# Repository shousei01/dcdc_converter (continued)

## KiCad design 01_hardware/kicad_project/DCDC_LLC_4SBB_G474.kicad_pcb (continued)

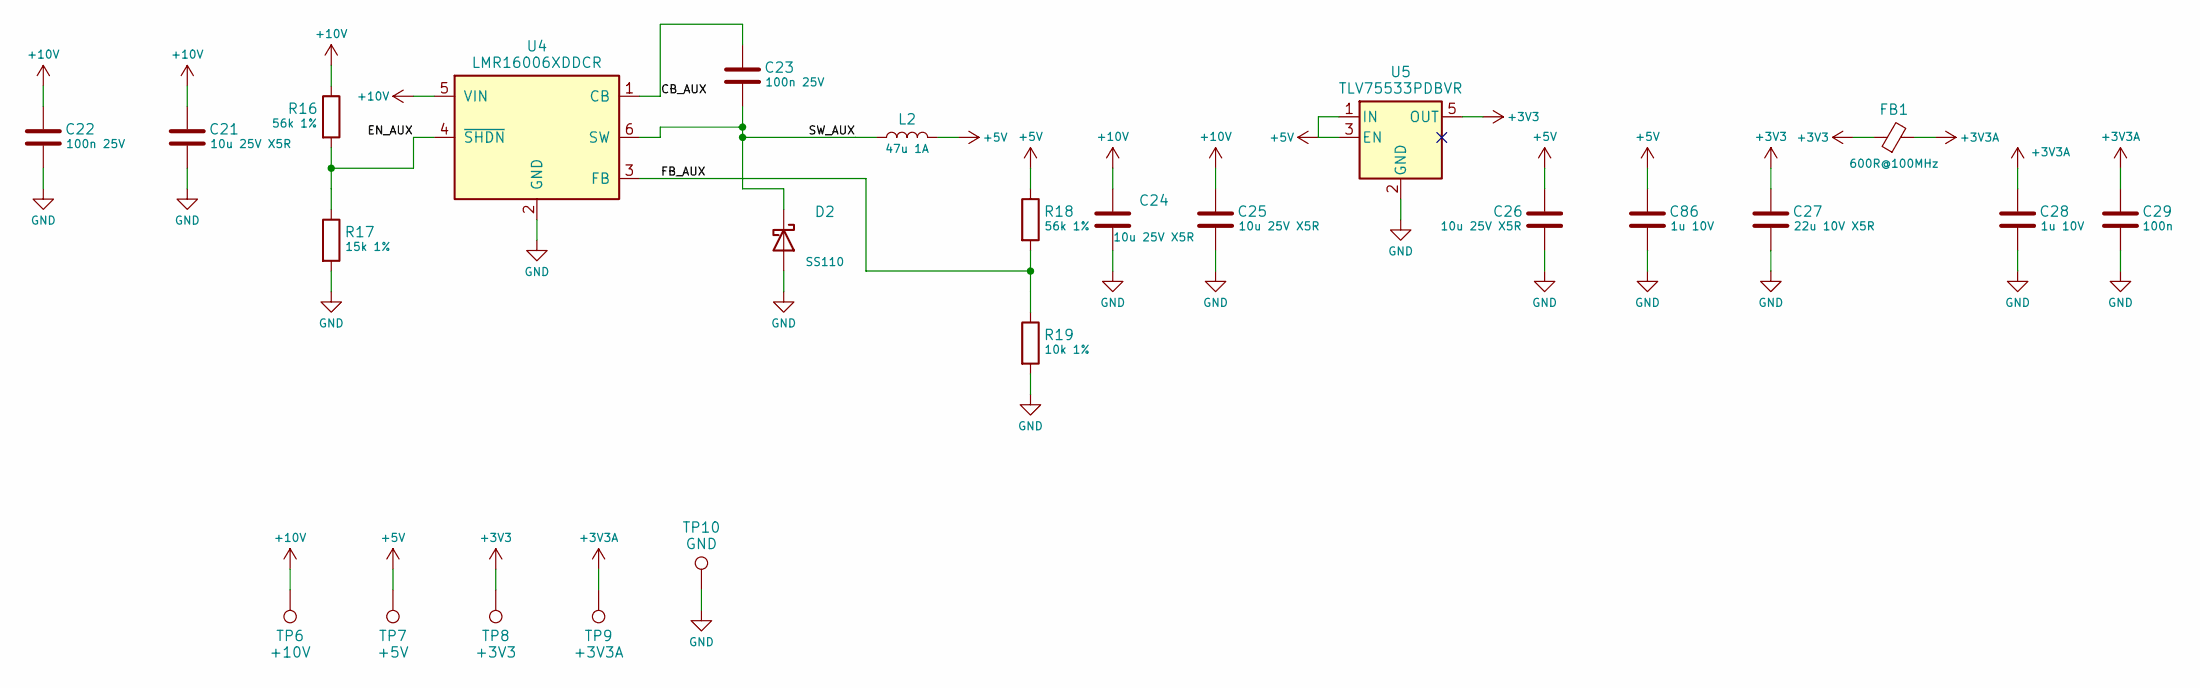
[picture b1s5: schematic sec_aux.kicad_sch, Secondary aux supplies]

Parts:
C21, C24, C25, C26: 10u 25V X5R; C_0805_2012Metric; MPN 10u 25V X5R; LCSC C15850
C22, C23: 100n 25V; C_0402_1005Metric; MPN 100n 25V; LCSC C307331
C27: 22u 10V X5R; C_0805_2012Metric; MPN 22u 10V X5R; LCSC C45783
C28, C86: 1u 10V; C_0402_1005Metric; MPN 1u 10V; LCSC C20539426
C29: 100n; C_0402_1005Metric; MPN 100n; LCSC C307331
D2: SS110; D_SMA; MPN SS110; LCSC C2482
FB1: 600R@100MHz; L_0603_1608Metric; MPN BLM18KG601SN1D; LCSC C85833
L2: 47u 1A; L_Sunlord_SWPA5040S; MPN FNR5040S470MT; LCSC C167974
R16, R18: 56k 1%; R_0402_1005Metric; MPN 56k 1%; LCSC C25796
R17: 15k 1%; R_0402_1005Metric; MPN 15k 1%; LCSC C25756
R19: 10k 1%; R_0402_1005Metric; MPN 10k 1%; LCSC C2906861
TP6: +10V; TestPoint_Pad_D1.5mm; MPN PCB pad, no part
TP7: +5V; TestPoint_Pad_D1.5mm; MPN PCB pad, no part
TP8: +3V3; TestPoint_Pad_D1.5mm; MPN PCB pad, no part
TP9: +3V3A; TestPoint_Pad_D1.5mm; MPN PCB pad, no part
TP10: GND; TestPoint_Pad_D1.5mm; MPN PCB pad, no part
U4: LMR16006XDDCR; SOT-23-6; MPN LMR16006XDDCR; LCSC C87080
U5: TLV75533PDBVR; SOT-23-5; MPN TLV75533PDBVR; LCSC C404027

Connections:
+3V3: C27.1, FB1.1, TP8.1, U5.5 (OUT); also elsewhere on the board
+3V3A: C28.1, C29.1, FB1.2, TP9.1; also elsewhere on the board
+5V: C26.1, C86.1, L2.2, R18.1, TP7.1, U5.1 (IN), U5.3 (EN); also elsewhere on the board
+10V: C21.1, C22.1, C24.1, C25.1, R16.1, TP6.1, U4.5 (VIN); also elsewhere on the board
CB_AUX: C23.1, U4.1 (CB)
EN_AUX: R16.2, R17.1, U4.4 (~SHDN)
FB_AUX: R18.2, R19.1, U4.3 (FB)
GND: C21.2, C22.2, C24.2, C25.2, C26.2, C27.2, C28.2, C29.2, C86.2, D2.2 (A), R17.2, R19.2, TP10.1, U4.2 (GND), U5.2 (GND); also elsewhere on the board
SW_AUX: C23.2, D2.1 (K), L2.1, U4.6 (SW)

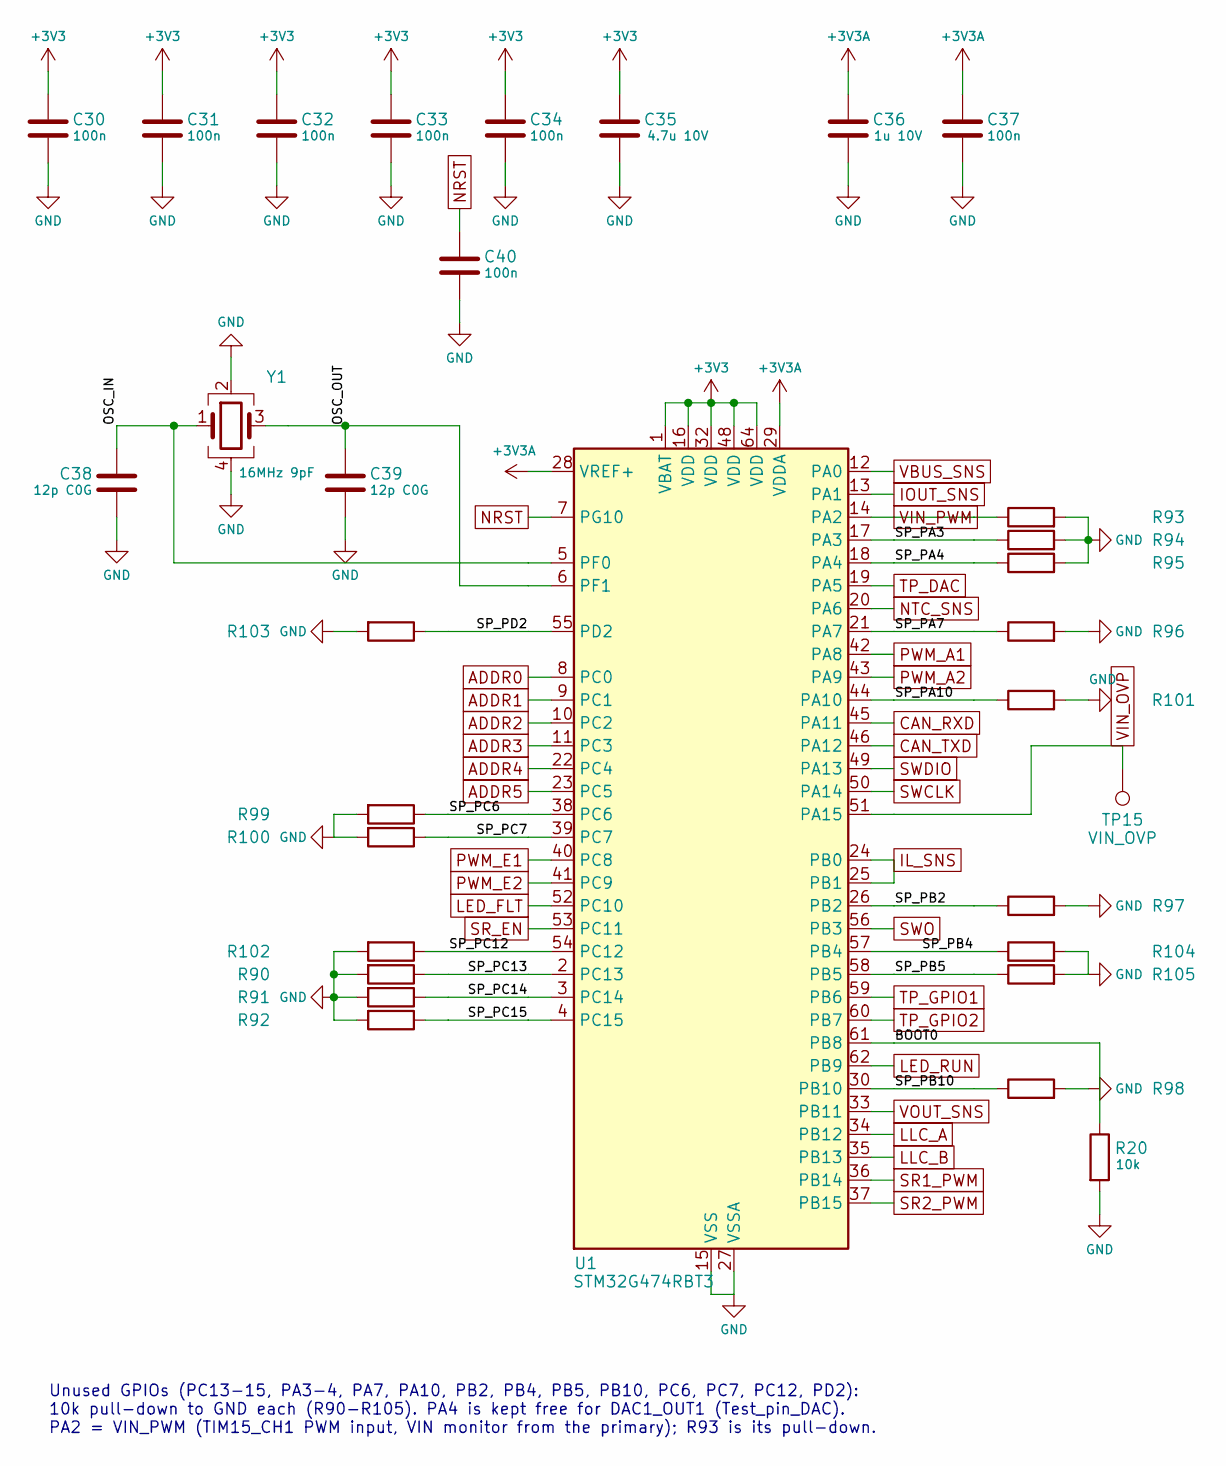
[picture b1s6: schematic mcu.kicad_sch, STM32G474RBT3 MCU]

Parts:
C30, C31, C32, C33, C34, C37, C40: 100n; C_0402_1005Metric; MPN 100n; LCSC C307331
C35: 4.7u 10V; C_0603_1608Metric; MPN 4.7u 10V; LCSC C19666
C36: 1u 10V; C_0402_1005Metric; MPN 1u 10V; LCSC C20539426
C38, C39: 12p C0G; C_0402_1005Metric; MPN 12p C0G; LCSC C1547
R20, R90, R91, R92, R93, R94, R95, R96, R97, R98, R99, R100, R101, R102, R103, R104, R105: 10k; R_0402_1005Metric; MPN 10k; LCSC C2906861
TP15: VIN_OVP; TestPoint_Pad_D1.5mm; MPN PCB pad, no part
U1: STM32G474RBT3; LQFP-64_10x10mm_P0.5mm; MPN STM32G474RBT3; LCSC C1235414
Y1: 16MHz 9pF; Crystal_SMD_3225-4Pin_3.2x2.5mm; MPN X322516MLB4SI; LCSC C13738

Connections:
+3V3: C30.1, C31.1, C32.1, C33.1, C34.1, C35.1, U1.1 (VBAT), U1.16 (VDD), U1.32 (VDD), U1.48 (VDD), U1.64 (VDD); also elsewhere on the board
+3V3A: C36.1, C37.1, U1.28 (VREF+), U1.29 (VDDA); also elsewhere on the board
ADDR0: U1.8 (PC0); also elsewhere on the board
ADDR1: U1.9 (PC1); also elsewhere on the board
ADDR2: U1.10 (PC2); also elsewhere on the board
ADDR3: U1.11 (PC3); also elsewhere on the board
ADDR4: U1.22 (PC4); also elsewhere on the board
ADDR5: U1.23 (PC5); also elsewhere on the board
BOOT0: R20.1, U1.61 (PB8)
CAN_RXD: U1.45 (PA11); also elsewhere on the board
CAN_TXD: U1.46 (PA12); also elsewhere on the board
GND: C30.2, C31.2, C32.2, C33.2, C34.2, C35.2, C36.2, C37.2, C38.2, C39.2, C40.2, R20.2, R90.2, R91.2, R92.2, R93.2, R94.2, R95.2, R96.2, R97.2, R98.2, R99.2, R100.2, R101.2, R102.2, R103.2, R104.2, R105.2, U1.15 (VSS), U1.27 (VSSA), U1.31 (VSS), U1.47 (VSS), U1.63 (VSS), Y1.2, Y1.4; also elsewhere on the board
IL_SNS: U1.24 (PB0), U1.25 (PB1); also elsewhere on the board
IOUT_SNS: U1.13 (PA1); also elsewhere on the board
LED_FLT: U1.52 (PC10); also elsewhere on the board
LED_RUN: U1.62 (PB9); also elsewhere on the board
LLC_A: U1.34 (PB12); also elsewhere on the board
LLC_B: U1.35 (PB13); also elsewhere on the board
NRST: C40.1, U1.7 (PG10); also elsewhere on the board
NTC_SNS: U1.20 (PA6); also elsewhere on the board
OSC_IN: C38.1, U1.5 (PF0), Y1.1
OSC_OUT: C39.1, U1.6 (PF1), Y1.3
PWM_A1: U1.42 (PA8); also elsewhere on the board
PWM_A2: U1.43 (PA9); also elsewhere on the board
PWM_E1: U1.40 (PC8); also elsewhere on the board
PWM_E2: U1.41 (PC9); also elsewhere on the board
SP_PA3: R94.1, U1.17 (PA3)
SP_PA4: R95.1, U1.18 (PA4)
SP_PA7: R96.1, U1.21 (PA7)
SP_PA10: R101.1, U1.44 (PA10)
SP_PB2: R97.1, U1.26 (PB2)
SP_PB4: R104.1, U1.57 (PB4)
SP_PB5: R105.1, U1.58 (PB5)
SP_PB10: R98.1, U1.30 (PB10)
SP_PC6: R99.1, U1.38 (PC6)
SP_PC7: R100.1, U1.39 (PC7)
SP_PC12: R102.1, U1.54 (PC12)
SP_PC13: R90.1, U1.2 (PC13)
SP_PC14: R91.1, U1.3 (PC14)
SP_PC15: R92.1, U1.4 (PC15)
SP_PD2: R103.1, U1.55 (PD2)
SR1_PWM: U1.36 (PB14); also elsewhere on the board
SR2_PWM: U1.37 (PB15); also elsewhere on the board
SR_EN: U1.53 (PC11); also elsewhere on the board
SWCLK: U1.50 (PA14); also elsewhere on the board
SWDIO: U1.49 (PA13); also elsewhere on the board
SWO: U1.56 (PB3); also elsewhere on the board
TP_DAC: U1.19 (PA5); also elsewhere on the board
TP_GPIO1: U1.59 (PB6); also elsewhere on the board
TP_GPIO2: U1.60 (PB7); also elsewhere on the board
VBUS_SNS: U1.12 (PA0); also elsewhere on the board
VIN_OVP: TP15.1, U1.51 (PA15); also elsewhere on the board
VIN_PWM: R93.1, U1.14 (PA2); also elsewhere on the board
VOUT_SNS: U1.33 (PB11); also elsewhere on the board

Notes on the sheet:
Unused GPIOs (PC13-15, PA3-4, PA7, PA10, PB2, PB4, PB5, PB10, PC6, PC7, PC12, PD2): 10k pull-down to GND each (R90-R105). PA4 is kept free for DAC1_OUT1 (Test_pin_DAC). PA2 = VIN_PWM (TIM15_CH1 PWM input, VIN monitor from the primary); R93 is its pull-down.

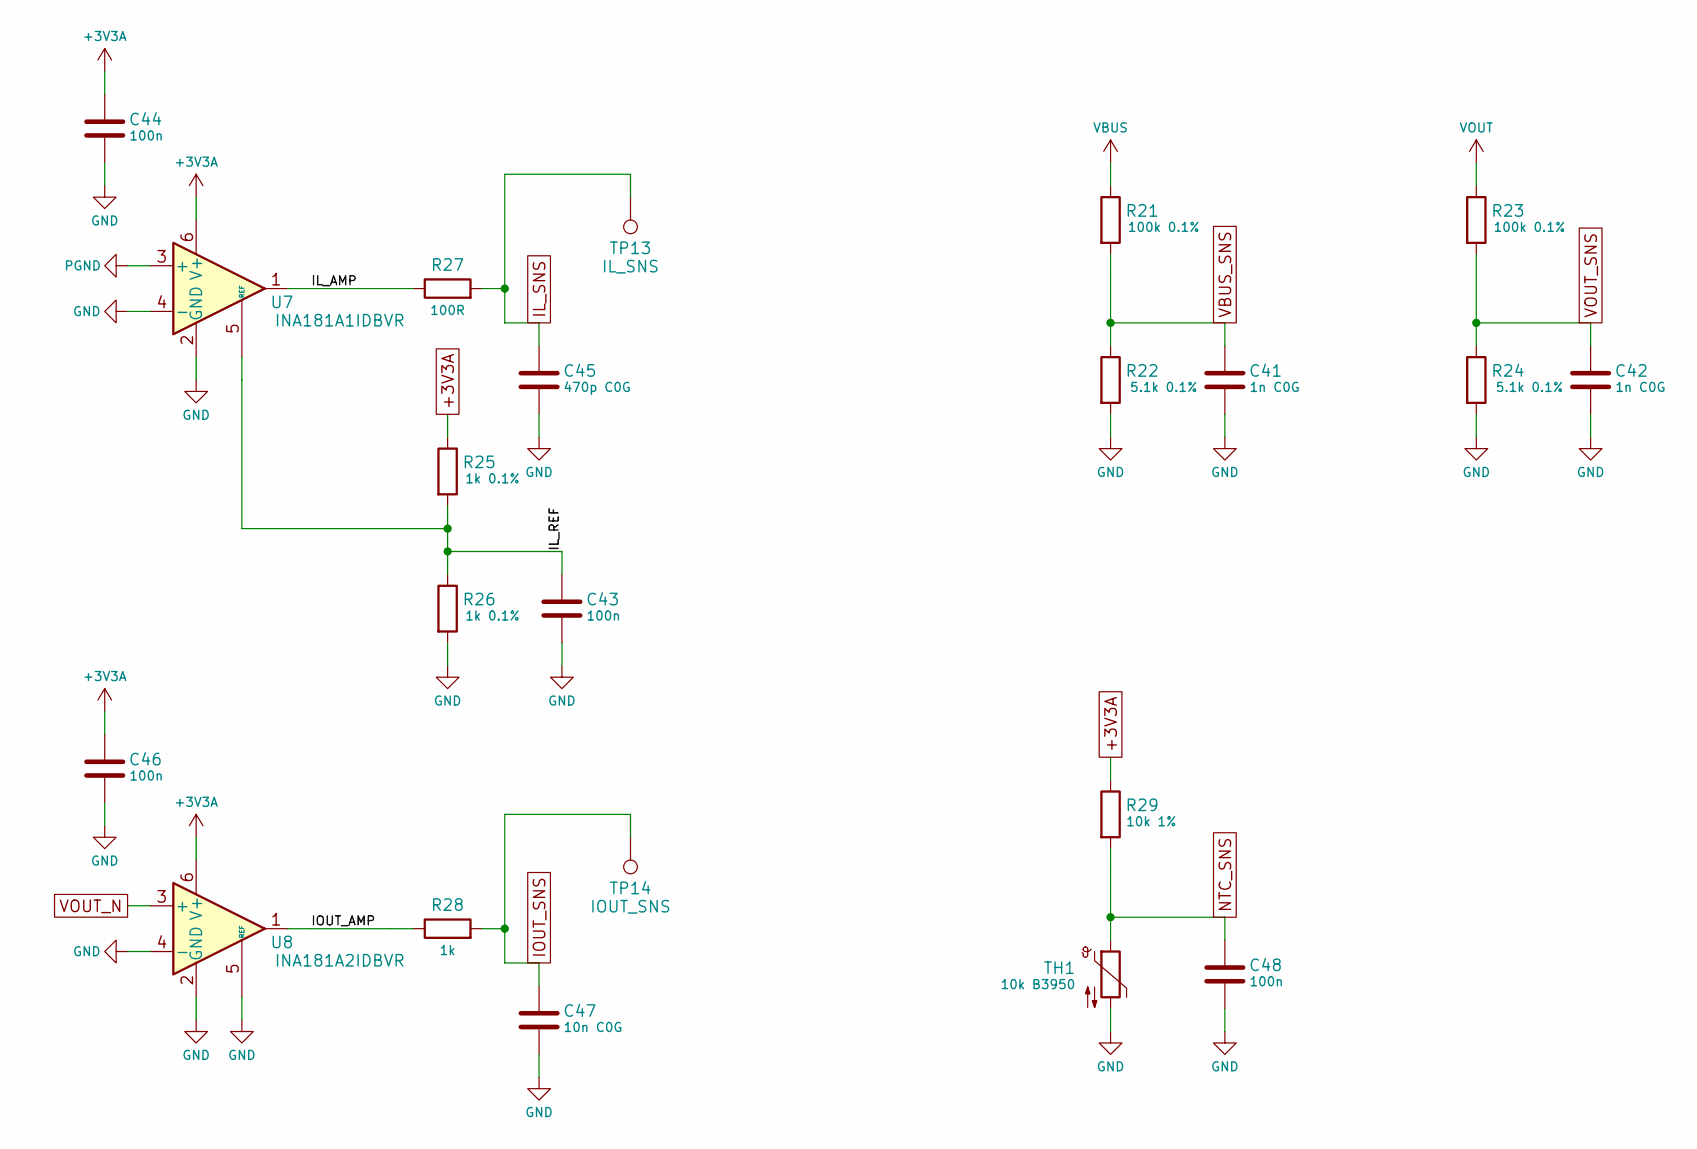
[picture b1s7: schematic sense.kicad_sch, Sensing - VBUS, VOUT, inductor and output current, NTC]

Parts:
C41, C42: 1n C0G; C_0402_1005Metric; MPN 1n C0G; LCSC C113780
C43, C44, C46, C48: 100n; C_0402_1005Metric; MPN 100n; LCSC C307331
C45: 470p C0G; C_0402_1005Metric; MPN 470p C0G; LCSC C106259
C47: 10n C0G; C_0402_1005Metric; MPN 10n C0G; LCSC C22400107
R21, R23: 100k 0.1%; R_0603_1608Metric; MPN 100k 0.1%; LCSC C122538
R22, R24: 5.1k 0.1%; R_0402_1005Metric; MPN 5.1k 0.1%; LCSC C186154
R25, R26: 1k 0.1%; R_0402_1005Metric; MPN 1k 0.1%; LCSC C186137
R27: 100R; R_0402_1005Metric; MPN 100R; LCSC C25076
R28: 1k; R_0402_1005Metric; MPN 1k; LCSC C11702
R29: 10k 1%; R_0402_1005Metric; MPN 10k 1%; LCSC C2906861
TH1: 10k B3950; R_0603_1608Metric; MPN 10k B3950; LCSC C2892547
TP13: IL_SNS; TestPoint_Pad_D1.5mm; MPN PCB pad, no part
TP14: IOUT_SNS; TestPoint_Pad_D1.5mm; MPN PCB pad, no part
U7: INA181A1IDBVR; SOT-23-6; MPN INA181A1IDBVR; LCSC C2058943
U8: INA181A2IDBVR; SOT-23-6; MPN INA181A2IDBVR; LCSC C2058784

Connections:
+3V3A: C44.1, C46.1, R25.1, R29.1, U7.6 (V+), U8.6 (V+); also elsewhere on the board
GND: C41.2, C42.2, C43.2, C44.2, C45.2, C46.2, C47.2, C48.2, R22.2, R24.2, R26.2, TH1.2, U7.2 (GND), U7.4 (-), U8.2 (GND), U8.4 (-), U8.5 (REF); also elsewhere on the board
IL_AMP: R27.1, U7.1
IL_REF: C43.1, R25.2, R26.1, U7.5 (REF)
IL_SNS: C45.1, R27.2, TP13.1; also elsewhere on the board
IOUT_AMP: R28.1, U8.1
IOUT_SNS: C47.1, R28.2, TP14.1; also elsewhere on the board
NTC_SNS: C48.1, R29.2, TH1.1; also elsewhere on the board
PGND: U7.3 (+); also elsewhere on the board
VBUS: R21.1; also elsewhere on the board
VBUS_SNS: C41.1, R21.2, R22.1; also elsewhere on the board
VOUT: R23.1; also elsewhere on the board
VOUT_N: U8.3 (+); also elsewhere on the board
VOUT_SNS: C42.1, R23.2, R24.1; also elsewhere on the board

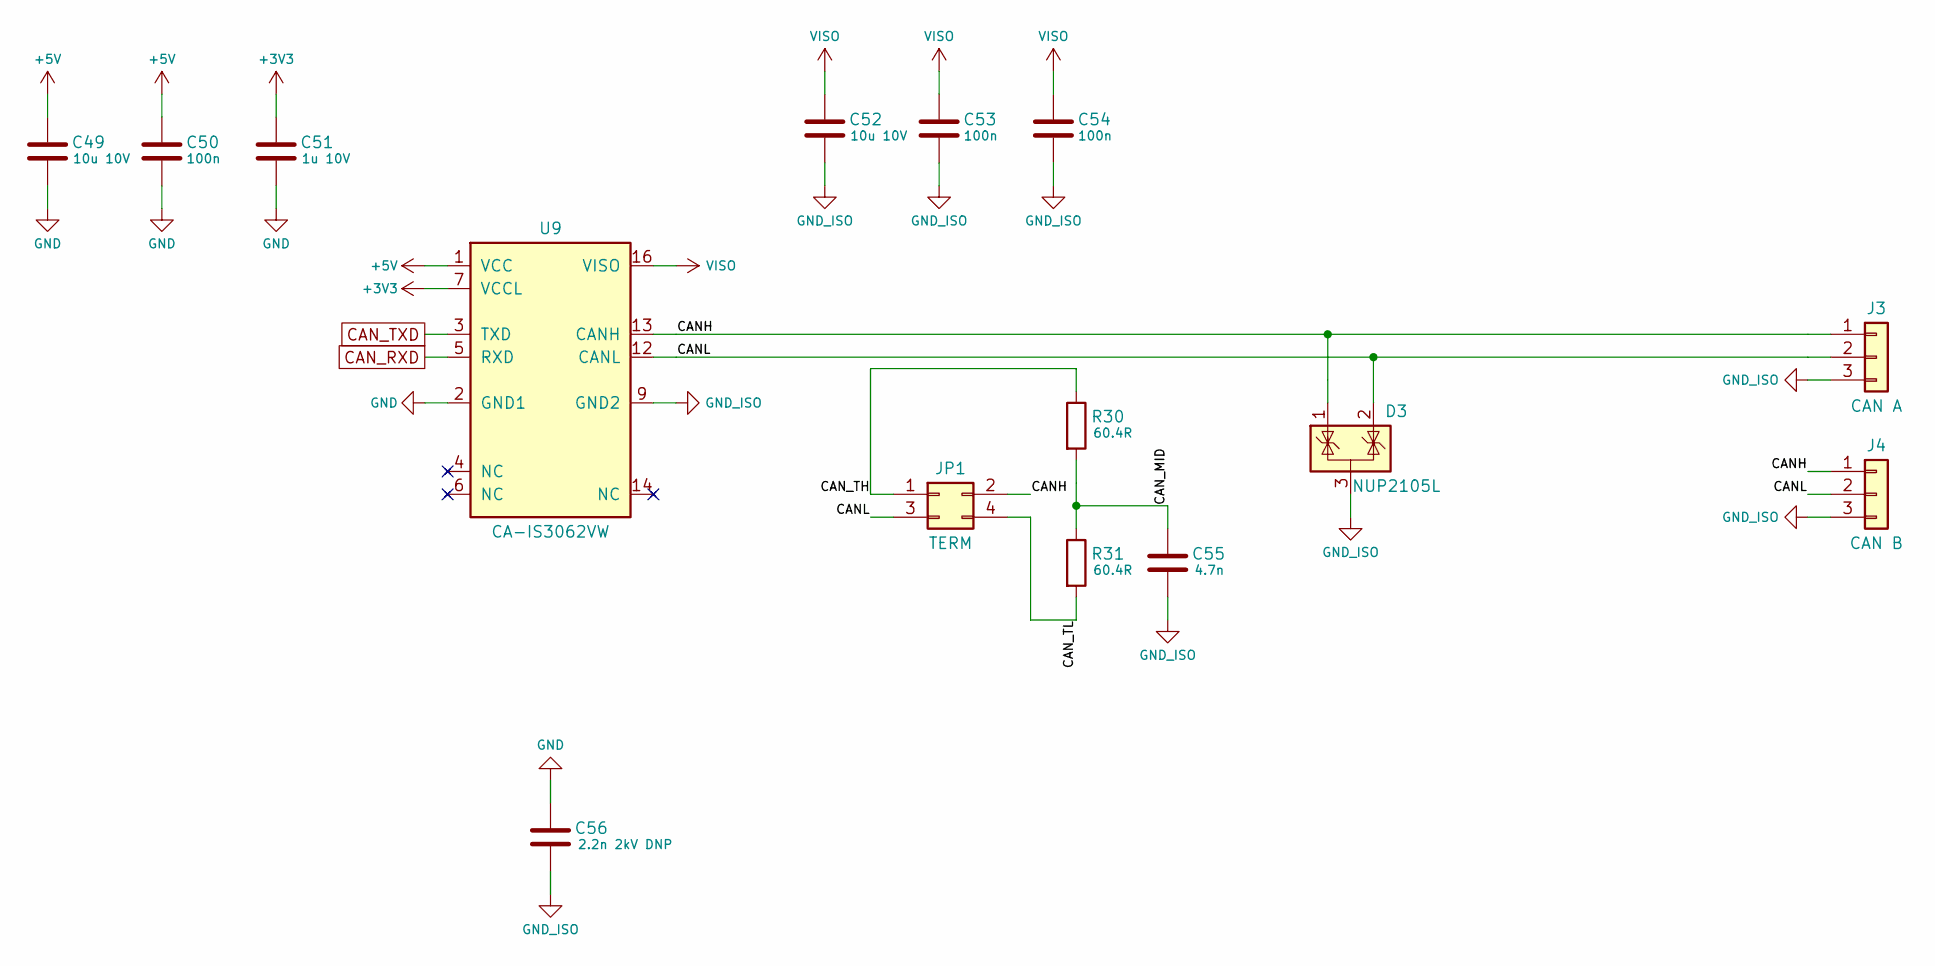
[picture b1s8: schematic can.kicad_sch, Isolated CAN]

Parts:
C49, C52: 10u 10V; C_0805_2012Metric; MPN 10u 10V; LCSC C15850
C50, C53, C54: 100n; C_0402_1005Metric; MPN 100n; LCSC C307331
C51: 1u 10V; C_0402_1005Metric; MPN 1u 10V; LCSC C20539426
C55: 4.7n; C_0603_1608Metric; MPN 4.7n; LCSC C53987
C56: 2.2n 2kV DNP; C_Disc_D8.0mm_W5.0mm_P7.50mm; MPN 2.2n 2kV DNP
D3: NUP2105L; SOT-23; MPN NUP2105LT1G; LCSC C14486
J3: CAN A; PinHeader_1x03_P2.54mm_Vertical; MPN PZ254V-11-03P-A40; LCSC C42419910
J4: CAN B; PinHeader_1x03_P2.54mm_Vertical; MPN PZ254V-11-03P-A40; LCSC C42419910
JP1: TERM; PinHeader_2x02_P2.54mm_Vertical; MPN PZ254V-12-04P-A40; LCSC C45384660
R30, R31: 60.4R; R_0603_1608Metric; MPN 60.4R; LCSC C2933247
U9: CA-IS3062VW; SOIC-16W_7.5x10.3mm_P1.27mm; MPN CA-IS3062VW; LCSC C5338808

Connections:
+3V3: C51.1, U9.7 (VCCL); also elsewhere on the board
+5V: C49.1, C50.1, U9.1 (VCC); also elsewhere on the board
CANH: D3.1 (K), J3.1, J4.1, JP1.2, U9.13 (CANH)
CANL: D3.2 (K), J3.2, J4.2, JP1.3, U9.12 (CANL)
CAN_MID: C55.1, R30.2, R31.1
CAN_RXD: U9.5 (RXD); also elsewhere on the board
CAN_TH: JP1.1, R30.1
CAN_TL: JP1.4, R31.2
CAN_TXD: U9.3 (TXD); also elsewhere on the board
GND: C49.2, C50.2, C51.2, C56.1, U9.2 (GND1), U9.8 (GND1); also elsewhere on the board
GND_ISO: C52.2, C53.2, C54.2, C55.2, C56.2, D3.3 (A), J3.3, J4.3, U9.9 (GND2), U9.10 (GND2), U9.15 (GND2)
VISO: C52.1, C53.1, C54.1, U9.11 (VISO), U9.16 (VISO)

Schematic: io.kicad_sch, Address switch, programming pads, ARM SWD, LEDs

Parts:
D4: GREEN RUN; LED_0603_1608Metric; MPN GREEN RUN; LCSC C12624
D5: RED FAULT; LED_0603_1608Metric; MPN RED FAULT; LCSC C2286
H1, H2, H3, H4: M3; MountingHole_3.2mm_M3; MPN no part (M3 standoff hole)
J5: ADDR HDR; PinHeader_1x06_P2.54mm_Vertical; MPN PZ254V-11-06P-A40; LCSC C42419913
J6: PROG PADS; TestPads_1x08_P2.54mm_D2.0mm; MPN PROG PADS
J7: ARM SWD 10; PinHeader_2x05_P1.27mm_Vertical_SMD; MPN HX PZ1.27-2x5P TP; LCSC C41376037
R32, R33, R34, R35, R36, R37: 10k; R_0402_1005Metric; MPN 10k; LCSC C2906861
R38, R39, R40, R41, R42, R43, R44, R45: 1k; R_0402_1005Metric; MPN 1k; LCSC C11702
R123, R124, R125, R126, R127, R128: 47.5R 1%; R_0402_1005Metric; MPN 0402WGF475JTCE; LCSC C82290
R129: 2R 1%; R_0603_1608Metric; MPN FRC0603F2R00TS; LCSC C2933191
SW1: DIP-6; SW_DIP_SPSTx06_Slide_6.7x16.8mm_W8.61mm_P2.54mm_LowProfile; MPN DIP-6; LCSC C6331172

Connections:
+3V3: D4.2 (A), D5.2 (A), R32.2, R33.2, R34.2, R35.2, R36.2, R37.2, R129.1; also elsewhere on the board
ADDR0: R32.1, R38.2, SW1.1; also elsewhere on the board
ADDR1: R33.1, R39.2, SW1.2; also elsewhere on the board
ADDR2: R34.1, R40.2, SW1.3; also elsewhere on the board
ADDR3: R35.1, R41.2, SW1.4; also elsewhere on the board
ADDR4: R36.1, R42.2, SW1.5; also elsewhere on the board
ADDR5: R37.1, R43.2, SW1.6; also elsewhere on the board
ADDR_H0: J5.1, R38.1
ADDR_H1: J5.2, R39.1
ADDR_H2: J5.3, R40.1
ADDR_H3: J5.4, R41.1
ADDR_H4: J5.5, R42.1
ADDR_H5: J5.6, R43.1
GND: J6.8, J7.3, J7.5, J7.9, SW1.7, SW1.8, SW1.9, SW1.10, SW1.11, SW1.12; also elsewhere on the board
LED_FLT: R45.2; also elsewhere on the board
LED_FLT_K: D5.1 (K), R45.1
LED_RUN: R44.2; also elsewhere on the board
LED_RUN_K: D4.1 (K), R44.1
NRST: R128.1; also elsewhere on the board
NRST_C: J6.6, J7.10, R128.2
PROG_3V3: J6.7, J7.1, R129.2
SWCLK: R124.1; also elsewhere on the board
SWCLK_C: J6.2, J7.4, R124.2
SWDIO: R123.1; also elsewhere on the board
SWDIO_C: J6.1, J7.2, R123.2
SWO: J7.6; also elsewhere on the board
TP_DAC: R125.1; also elsewhere on the board
TP_DAC_C: J6.3, R125.2
TP_GPIO1: R126.1; also elsewhere on the board
TP_GPIO1_C: J6.4, R126.2
TP_GPIO2: R127.1; also elsewhere on the board
TP_GPIO2_C: J6.5, R127.2

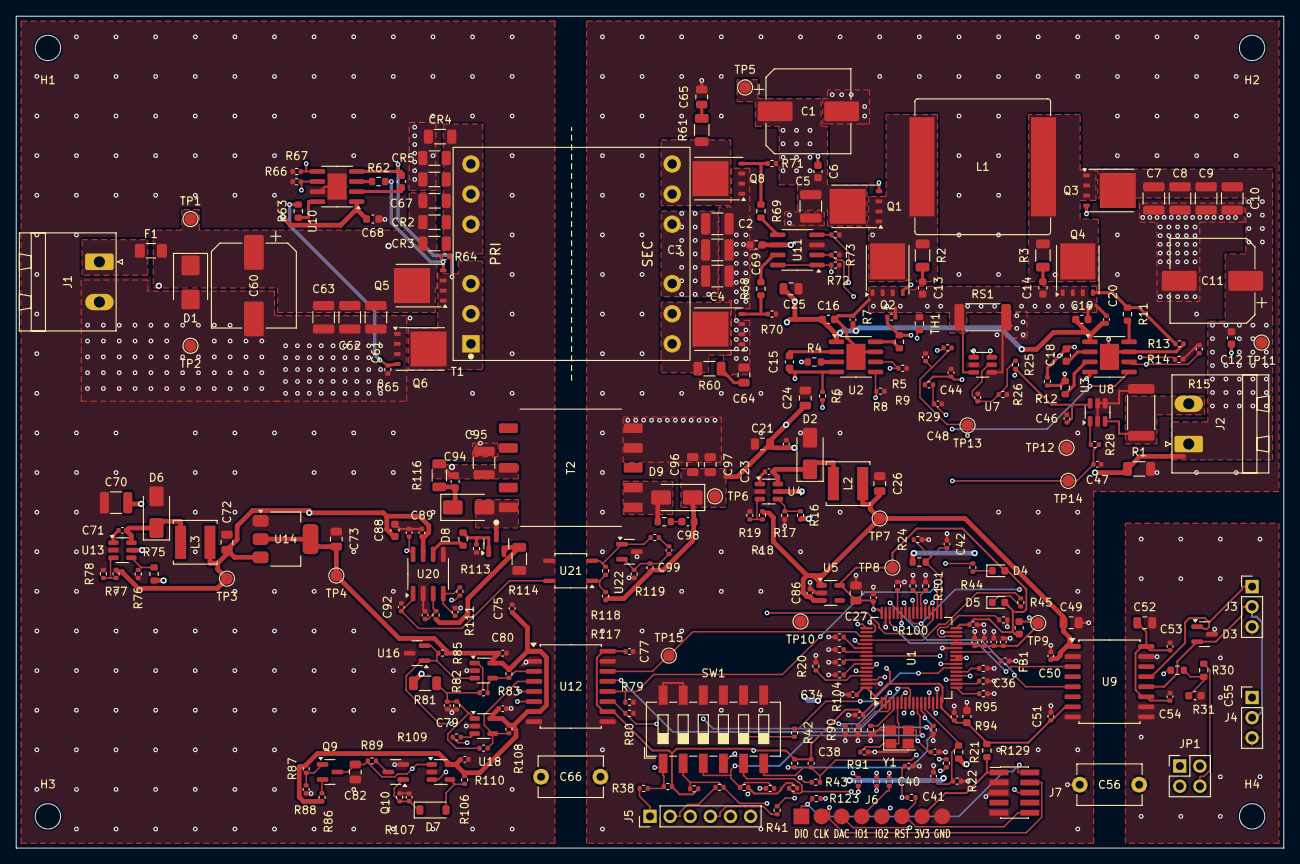
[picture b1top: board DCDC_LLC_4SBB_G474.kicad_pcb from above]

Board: 4 copper layers, 160.0 x 105.0 mm, 291 parts (0 on the bottom side), 155 nets.

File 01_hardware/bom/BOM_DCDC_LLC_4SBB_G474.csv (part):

Designator,Qty,Value,MPN,LCSC,Footprint,DNP,Unit_USD,Ext_USD,Price_source,Note
"C1,C11,C60",3,47u 63V,,C249664,CP_Elec_10x10.5,,0.1,0.3,est,"Isolated bus bulk (LLC output / 4SBB input), low-ESR"
"C2,C3,C4,C5,C7,C8,C9,C10,C61,C62,C63,C70,C95",13,2.2u 100V X7R,,C153036,C_1210_3225Metric,,0.3626,4.714,LCSC C153036 FS32X225K101EGG (C55151 Samsung out of stock),"Bus hot-loop MLCC, place at Q1 drain / RS; also LLC output caps"
"C6,C12",2,100n 100V X7R,,C88219,C_0603_1608Metric,,0.03,0.06,est,
"C13,C14",2,1n 100V DNP,,,C_0603_1608Metric,DNP,0.03,0,est,
"C15,C18,C67",3,100n 25V X7R,,C14663,C_0603_1608Metric,,0.003,0.009,est,Bootstrap cap
"C16,C19,C68,C69,C88",5,1u 25V X7R,,C15849,C_0603_1608Metric,,0.03,0.15,est,Driver VDD decoupling at pin 1-7
"C17,C20,C22,C23,C71,C89",6,100n 25V,,C307331,C_0402_1005Metric,,0.003,0.018,est,
"C21,C24,C25,C26,C72,C96,C97",7,10u 25V X5R,,C15850,C_0805_2012Metric,,0.03,0.21,est,"U4 input, at pin 5"
"C27,C73",2,22u 10V X5R,,C45783,C_0805_2012Metric,,0.003,0.006,est,
"C28,C36,C51,C86",4,1u 10V,,C20539426,C_0402_1005Metric,,0.003,0.012,est,U5 input
"C29,C30,C31,C32,C33,C34,C37,C40,C43,C44,C46,C48,C50,C53,C54,C75,C77,C80,C83,C84,C90,C99",22,100n,,C307331,C_0402_1005Metric,,0.003,0.066,est,
C35,1,4.7u 10V,,C19666,C_0603_1608Metric,,0.003,0.003,est,
"C38,C39",2,12p C0G,,C1547,C_0402_1005Metric,,0.003,0.006,est,
"C41,C42,C79,C91,C92",5,1n C0G,,C113780,C_0402_1005Metric,,0.003,0.015,est,
C45,1,470p C0G,,C106259,C_0402_1005Metric,,0.003,0.003,est,Keep RC fast (~47 ns) for comparator OCP
C47,1,10n C0G,,C22400107,C_0402_1005Metric,,0.003,0.003,est,
"C49,C52",2,10u 10V,,C15850,C_0805_2012Metric,,0.003,0.006,est,
C55,1,4.7n,,C53987,C_0603_1608Metric,,0.003,0.003,est,
C56,1,2.2n 2kV DNP,,,C_Disc_D8.0mm_W5.0mm_P7.50mm,DNP,0.003,0,est,Optional Y-cap for EMI
"C64,C65",2,1n 200V DNP,,,C_0805_2012Metric,DNP,0.003,0,est,
C66,1,1n Y1 DNP,,,C_Disc_D8.0mm_W5.0mm_P7.50mm,DNP,0.15,0,est,Optional pri-sec Y-cap for EMI: must be Y1/Y2 safety-rated if fitted; else leave empty
"C81,C93",2,220p C0G,,C107001,C_0402_1005Metric,,0.003,0.006,est,Reset hold ~20 us with R107; small so the gate charges fully (0.2 us) before U17 lets go
C82,1,47n C0G 25V,C0805C473F3GECAUTO,C2233314,C_0805_2012Metric,,0.003,0.003,est,Ramp capacitor - must be C0G (X7R bends the ramp)
C94,1,4.7n 100V X7R,,C115052,C_0603_1608Metric,,0.03,0.03,est,
C98,1,470p 100V DNP,,,C_0603_1608Metric,DNP,0.03,0,est,
"CR1,CR2,CR3,CR4,CR5,CR6",6,100n 100V C0G,,C2940749,C_1206_3216Metric,,0.08,0.48,"est, 1206 C0G","Split resonant cap, upper half (3 x 100 nF)"
D1,1,SMBJ51A,SMBJ51A,C20883337,D_SMB,,0.05,0.05,est,"Unidirectional TVS, 51 V standoff, 82 V clamp; with F1 also clears reverse polarity"
"D2,D6,D8,D9",4,SS110,SS110,C2482,D_SMA,,0.03,0.12,est,Schottky catch diode
D3,1,NUP2105L,NUP2105LT1G,C14486,SOT-23,,0.06,0.06,est,24 V CAN bus ESD/TVS
D4,1,GREEN RUN,,C12624,LED_0603_1608Metric,,0.01,0.01,est,
D5,1,RED FAULT,,C2286,LED_0603_1608Metric,,0.01,0.01,est,
D7,1,1N4148W,1N4148W,C81598,D_SOD-123,,0.0,0.0,?,
F1,1,7A 63V,0458007.DR,C206980,Fuse_1206_3216Metric,,0.45,0.45,LCSC C206980 0458007.DR,Fast-acting 7 A 63 V 1206 chip fuse (Littelfuse 0458007.DR; 2nd source Schurter 3413.0326.11)
FB1,1,600R@100MHz,BLM18KG601SN1D,C85833,L_0603_1608Metric,,0.01,0.01,est,VDDA / VREF+ filter
J1,1,VIN 12-48V,KF2EDGR-5.08-2P,C441204,"PhoenixContact_MSTBA_2,5_2-G-5,08_1x02_P5.08mm_Horizontal",,0.25,0.25,est,"Input: 5.08 mm pluggable male header (mates KF2EDGK plug), 12 A. PRIMARY side"
J2,1,VOUT 1.5-48V,KF2EDGR-5.08-2P,C441204,"PhoenixContact_MSTBA_2,5_2-G-5,08_1x02_P5.08mm_Horizontal",,0.25,0.25,est,"Output: 5.08 mm pluggable male header, 12 A"
J3,1,CAN A,PZ254V-11-03P-A40,C42419910,PinHeader_1x03_P2.54mm_Vertical,,0.04,0.04,est,CAN in
J4,1,CAN B,PZ254V-11-03P-A40,C42419910,PinHeader_1x03_P2.54mm_Vertical,,0.04,0.04,est,CAN out (daisy-chain)
J5,1,ADDR HDR,PZ254V-11-06P-A40,C42419913,PinHeader_1x06_P2.54mm_Vertical,,0.05,0.05,est,Shorting a pin to GND (via harness) sets bit = 0; parallel with SW1
J7,1,ARM SWD 10,HX PZ1.27-2x5P TP,C41376037,PinHeader_2x05_P1.27mm_Vertical_SMD,,0.4,0.4,"est, 2x5 1.27 mm SMD header","ARM Cortex Debug 10-pin, 1.27 mm (1 VTref, 2 SWDIO, 4 SWCLK, 6 SWO, 10 nRESET, 7 key)"
JP1,1,TERM,PZ254V-12-04P-A40,C45384660,PinHeader_2x02_P2.54mm_Vertical,,0.02,0.02,est,"2x2 header: fit 2 shunts (1-2 CANH, 3-4 CANL) on end-of-bus node; open = termination fully disconnected from both lines"
L1,1,22u 23A sat,PSPMAA1770-220M-CGP,C49308184,L_Bourns_SRP1770TA_16.9x16.9mm,,1.0,1.0,"LCSC C49308184 $1.06@30, $0.91@300","22 uH, Isat 23 A, Irms 12 A, DCR 25 mOhm; alt Bourns SRP1770TA-220M (same footprint)"
"L2,L3",2,47u 1A,FNR5040S470MT,C167974,L_Sunlord_SWPA5040S,,0.05,0.1,LCSC C167974 FNR5040S470MT,"47 uH, Isat >= 1 A, 5040 shielded (2nd source SRN5040-470M, NRS5040T470MMGK, NRSC5040-470M)"
"Q1,Q4",2,NCEP0140AG,NCEP0140AG,C503009,TDSON-8-1,,0.4,0.8,"LCSC C503009: $0.62@1, $0.286@1k -> ~0.40@100","Input leg high side: hard-switched in buck -> low Qgd part (100 V, 18 mOhm, 26 nC)"
"Q2,Q3,Q5,Q6",4,NCEP068N10G,NCEP068N10G,C503061,TDSON-8-1,,0.64,2.56,LCSC C503061 (2026-10-20),"Input leg low side: sync rectifier in buck at up to 5 A -> low Rds part (100 V, 8.5 mOhm)"
"Q7,Q8",2,BSC160N15NS5,BSC160N15NS5,C459172,TDSON-8-1,,0.7523,1.505,LCSC C459172,"SR, 150 V (sees 2 x Vbus = 95 V at 48 V in), 16 mOhm, 19 nC"
Q9,1,MMBT3906,MMBT3906,C53444,SOT-23,,0.0,0.0,?,Ramp current source
Q10,1,2N7002,2N7002,C8545,SOT-23,,0.0,0.0,?,Ramp reset switch
Q11,1,FDN86246,FDN86246,C891118,SOT-23,,0.0,0.0,?,"150 V, 1.6 A, 195 mOhm N-MOSFET (Vds max ~95 V incl. clamp at 50 V in)"
R1,1,47k,,C2907507,R_1206_3216Metric,,0.003,0.003,est,Output pre-load / bleeder (49 mW at 48 V)
"R2,R3",2,2R2 DNP,,,R_1206_3216Metric,DNP,0.003,0,est,
"R4,R5,R10,R11,R68,R69",6,4R7,,C23164,R_0603_1608Metric,,0.003,0.018,est,High-side gate resistor
"R6,R7,R8,R9,R12,R13,R14,R15,R20,R32,R33,R34,R35,R36,R37,R64,R65,R66,R67,R70,R71,R72,R73,R74,R79,R80,R83,R90,R91,R92,R93,R94,R95,R96,R97,R98,R99,R100,R101,R102,R103,R104,R105,R108,R113",45,10k,,C2906861,R_0402_1005Metric,,0.003,0.135,est,Gate-source pull-down
"R16,R18,R86",3,56k 1%,,C25796,R_0402_1005Metric,,0.003,0.009,est,EN divider: U4 starts at ~6 V of the +10 V rail
"R17,R88",2,15k 1%,,C25756,R_0402_1005Metric,,0.003,0.006,est,
"R19,R29,R78,R87,R111,R120",6,10k 1%,,C2906861,R_0402_1005Metric,,0.003,0.018,est,
"R21,R23",2,100k 0.1%,,C122538,R_0603_1608Metric,,0.02,0.04,est,Isolated bus ~= VIN (DCX ratio 1); FS 68.0 V at 3.3 V VREF+
"R22,R24",2,5.1k 0.1%,,C186154,R_0402_1005Metric,,0.02,0.04,est,
"R25,R26",2,1k 0.1%,,C186137,R_0402_1005Metric,,0.02,0.04,est,"IL zero = VREF+/2, ratiometric"
R27,1,100R,,C25076,R_0402_1005Metric,,0.003,0.003,est,
"R28,R38,R39,R40,R41,R42,R43,R44,R45,R85,R106,R109,R115,R118",14,1k,,C11702,R_0402_1005Metric,,0.003,0.042,est,
"R30,R31",2,60.4R,,C2933247,R_0603_1608Metric,,0.003,0.006,est,"Split termination, enabled by JP1 (both jumpers)"
"R60,R61",2,4R7 DNP,,,R_1206_3216Metric,DNP,0.003,0,est,"SR snubber, fit only if ringing measured"
"R62,R63",2,2R2,,C2907006,R_0603_1608Metric,,0.003,0.006,est,
R75,1,470k,,C23178,R_0603_1608Metric,,0.003,0.003,est,Primary UVLO ~9.7 V
R76,1,68k,,C36871,R_0402_1005Metric,,0.003,0.003,est,
R77,1,120k 1%,,C25750,R_0402_1005Metric,,0.003,0.003,est,
R81,1,191k 0.1%,,C870479,R_1206_3216Metric,,0.02,0.02,est,"OVP / VIN-monitor divider top: OVP trips at 50.26 V rising, 49.83 V falling (R84, R110 included); 0.1 % sets the VIN reading accuracy"
R82,1,10k 0.1%,,C844452,R_0402_1005Metric,,0.02,0.02,est,
R84,1,2.2M,,C11490,R_0402_1005Metric,,0.003,0.003,est,Hysteresis ~0.4 V at VIN
R89,1,22R,,C2929994,R_0402_1005Metric,,0.003,0.003,est,Limits discharge peak current
R107,1,100k,,C25741,R_0402_1005Metric,,0.003,0.003,est,
R110,1,4.7M,,C227116,R_0402_1005Metric,,0.003,0.003,est,~10 mV hysteresis on the divider side; does not load the ramp
R112,1,10R,,C22859,R_0603_1608Metric,,0.003,0.003,est,Gate resistor
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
